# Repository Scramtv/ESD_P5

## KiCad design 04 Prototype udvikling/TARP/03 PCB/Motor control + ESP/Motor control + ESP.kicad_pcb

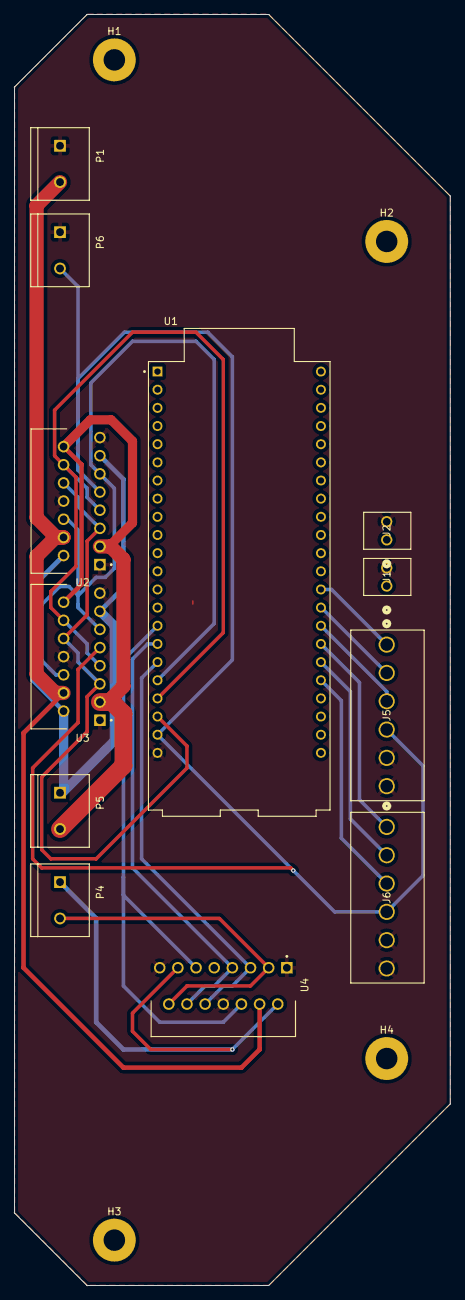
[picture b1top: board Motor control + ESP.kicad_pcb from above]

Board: 2 copper layers, 61.0 x 177.8 mm, 16 parts (0 on the bottom side), 21 nets.

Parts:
H1, H2, H3, H4: MountingHole; MountingHole_3mm_Pad
J1: Button in2; CONN_A-6373-02A_MOL
J2: Button in1; CONN_A-6373-02A_MOL
J5: Encoder1; CONN_SDA-41791_M450_06_MOL
J6: Encoder2; CONN_SDA-41791_M450_06_MOL
P1: Volt supply; TE_282837-2
P4: Motor out2; TE_282837-2
P5: Motor out1; TE_282837-2
P6: Power in; TE_282837-2
U1: ESP32-S3-DEVKITM-1-N8; MODULE_ESP32-S3-DEVKITM-1-N8
U2, U3, U4: L298N; TO127P2020X500X2100-15

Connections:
+5V: J5.4, J6.4, P6.2, U1.J1_21 (5V0), U2.9 (Vss), U3.9 (Vss)
+12V: P1.2, U2.4 (Vs), U3.4 (Vs), U4.4 (Vs)
<NO NET>: J1.2, J2.2, J5.5, J5.6, J6.5, J6.6, P1.1, P6.1, U1.J1_22 (GND_J1_22), U2.1 (SENSE_A), U2.8 (GND), U2.15 (SENSE_B), U3.1 (SENSE_A), U3.8 (GND), U3.15 (SENSE_B), U4.1 (SENSE_A), U4.8 (GND), U4.15 (SENSE_B)
unnamed: U1.J1_15 (GPIO13), U4.6 (EnA), U4.11 (EnB)
unnamed: U1.J1_16 (GPIO14), U4.7 (IN2), U4.12 (IN4)
unnamed: U1.J1_17 (GPIO15), U4.5 (IN1), U4.10 (IN3)
unnamed: U1.J1_18 (GPIO16), U2.6 (EnA), U2.11 (EnB), U3.6 (EnA), U3.11 (EnB)
unnamed: U1.J1_19 (GPIO17), U2.7 (IN2), U2.12 (IN4), U3.7 (IN2), U3.12 (IN4)
unnamed: U1.J1_20 (GPIO18), U2.5 (IN1), U2.10 (IN3), U3.5 (IN1), U3.10 (IN3)
unnamed: J6.3, U1.J3_18 (GPIO21)
unnamed: J6.2, U1.J3_17 (GPIO26)
unnamed: J6.1, U1.J3_16 (GPIO33)
unnamed: J5.3, U1.J3_15 (GPIO34)
unnamed: J5.2, U1.J3_14 (GPIO35)
unnamed: J5.1, U1.J3_13 (GPIO36)
unnamed: J1.1, U1.J3_12 (GPIO37)
unnamed: J2.1, U1.J3_11 (GPIO38)
unnamed: P5.1, U2.2 (OUT1), U2.13 (OUT3), U3.2 (OUT1), U3.13 (OUT3)
unnamed: P5.2, U2.3 (OUT2), U2.14 (OUT4), U3.3 (OUT2), U3.14 (OUT4)
unnamed: P4.1, U4.2 (OUT1), U4.13 (OUT3)
unnamed: P4.2, U4.3 (OUT2), U4.14 (OUT4)

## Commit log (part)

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2025-10-28 Antenna 0 and 1 CST (1 til1)
2025-10-28 Matlab plotter til antenne 0 og 1
2025-10-28 Opdateringf motor parameter test
    Opdatering af matlab fill og slet dublicate script
2025-10-28 Antenne Matlab - plotter og data
2025-10-28 Data til model af tilt motor inkl. behandling
2025-10-29 Parameter kode opdateret til support af "tick" pin
    Udover det er koden også generelt opryddet, så vi kun har de funktioner der er blevet brugt
2025-10-29 Model for både Azi og tilt motor inkl. load
2025-10-30 Gaintest Antenna1
2025-10-30 PNG files of simulated and measured S-11 of Antenna 0 and titlechanges for corresponding matlab script
2025-10-30 TARP Motor code v1.1 - WORKS
    - Added state machine
    - works, but does not constantly keep in check with its position. If it is moved, it does not auto correct
2025-10-30 1x2 fælles kanal m. stub
2025-10-30 Referat fra vejledermøde 30-10-2025
2025-10-30 Forbedret formatering
2025-10-31 1x2Antenne V1
    Både opdateret sim og pcb
2025-11-03 Udregning og sim af P +(lead) controller til TARP
    NB lead er ikke helt færdig, men vi starter med at dokumentere P-controlleren
2025-11-03 Ugentlig opdatering af tidsplan iht. møde.
2025-11-03 Oprydning af filer
    TBH ved ikke helt hvordan denne har fundet vej til git, men den ryger ned nu :)
2025-11-04 Ændring af filstruktur og opdatering af gamle filer
    Jeg har ændret strukturen af antenne mapperne og slettet gamle ubrugte filer, der ikke indholdte relevante ting.
    Derudover har jeg også opdateret gamle CST filer så de er kompatible med voksen CST
2025-11-04 Draw.io fil brugt til RF front end udvikling
2025-11-04 Sletning af fejl program
2025-11-04 Ændring af fejl i interface guide til gnu
2025-11-04 TARP motor code V1.3
    - added 2 micro second delay to help with short circuit of H-bridge
    - Changed SSID from AP to TARP
2025-11-05 Opdatering af gamle antenne simulering med export af data, samt simulering af array
    Jeg har opdateret de resterende antenne simuleringer til at være kompatible med voksen CSV og eksporteret simuleringerne i txt format.
    Har også lavet hvad der burde blive arrayet.
2025-11-05 Flytning af diagrammer for frontend
2025-11-05 Upload af beam forming scripts
2025-11-05 H-bridge short circuit update
    - matlab with plots of the issue
    -- plots with potential fix of 1k
    -- BJT issue
    --- BJT potential fix with pull down resistors
    - clean up of data
2025-11-05 TARP motor code V1.4
    - Error margin set to 0
    - delay set to 3 microseconds
2025-11-05 Azimut Control test 80.35 Gain + plot
    Control test of TARP with Gain of 80.35
2025-11-05 Simulering af antenne 6 og videre arbejde på antenne mount
    Antenne 6 sigter efter at sænke frekvensen af antenne 5 med 10 MHz og udvide bundbredden i my.
    Der er nu en holder til antennen tegnet i SolidWorks, der skal bare laves noget til at klaske den på TARPen, samt et "låg" til holderen.
2025-11-06 Indsættelse af tidsbegrænsning på aflås lokale og fjernelse af "Læs opgaven"
2025-11-07 Stavefejl i bødesystem
2025-11-07 Test af antenne 4,5, 5.10 og 5.11
2025-11-07 Viderudvikling af front end. Undersøg muligheden for at trække data ud af GNU
2025-11-07 Ekstra figure til proposed solution. (Alså en ny figure men i samme dokument)
2025-11-09 Billeder af fysisk setup
2025-11-09 Omnavngivning og rettelse af regnefejl af motor parametre
2025-11-09 Billede af ustabile hastigheder for tiltmoteren
    NB lavet ved konstant spænding
2025-11-09 Opdatering af overføringsfunktioner, så de nu bruger korrekte modelparametre
2025-11-10 Updated git ignore to disregard matlab autosave
2025-11-10 Script to plot OL bode plot and CL step with P-controller
    Both for azi and tilt
2025-11-10 Ændringer til låget til antenne holderen
    Den er blevet gjort tykkere
2025-11-10 Opdatering så step respons er for 180 grader og ikke 1
2025-11-11 Opdatering af tidsplan iht. dagligt møde
2025-11-12 Serial R/W interface to ESP32
2025-11-13 Opdatering af git ignore til at undlade python temp files
2025-11-13 Interface for direct motor control via serialRW.py
    Can control both tilt and azimuth motor, can also return their position
2025-11-13 Udregninger på modtaget effekt og SNR
    Har slettet min temp maplefil og omdøbt SNR&SignalStrenth. Og selvfølgelig udregnet SNR
2025-11-13 ESP code kan nu håndtere begge kerner
    PT er der intet der kører på kernerne @MiniBeier indsætter sin kode heri
2025-11-13 TARP Motor code V2.0
    - tilt code added
    - new files for azimut, tilt and UART
    - change of button names and interrupts setup
2025-11-13 TARP Azimut step response 3.73 gain
2025-11-13 data fra beamsteering test
    - Jeppe
2025-11-13 TARP Motorcode V3.0
    - Integrated 2 cores
    - currently running one core
2025-11-14 Referat fra vejledermøde d. 13-11-2025
2025-11-14 TARP Motorcode V3.1_kommentarer
    Div. kommentarer. @MiniBeier kigger på disse
2025-11-14 Matlab plots til TARP control test
    - Korrekt gain
    - Kode V3.1 (skal opdateres til nyt kode)
2025-11-15 Slet af fejl kode og opdatering af ny kode
    -Jeppe på pi
2025-11-16 TARP Control code V3.2
    -Added sample rate control
    -Code clean up
    -- removal of state machine
    -- merging of velocity function
    --removal of irrelevant variables and functions
2025-11-16 Data til test af hvad der er galt med breamforming og frontend
    - Jeppe fra RPI
2025-11-17 Krav for detection time og precision
    Lavet på baggrund af krav i teams
2025-11-17 Opdatering af controller udregning
    Korrekte P-værdier
    notat om lead-controller
2025-11-17 Settlingtime for CL azi og tilt
2025-11-18 H-bridge diagram current flow
2025-11-18 TARP Control test of code V3.3
    - Matlab plots
    -- Step response tilt + azi
    - Data
    -- step response tilt + azi
    -- tilt slør
2025-11-19 Bruger korrekte tolerancer og nyt script til med større numerisk præcision
2025-11-19 Opdatering så stepresponse er for 90 grader og ikke 180
2025-11-21 Fix af beregninger
    Havde nogle beregninger der ikek var rigtige, nu er de
2025-11-24 Added zoom for open loop bodeplot
    Based on comment from Jesper
2025-11-24 H-bridge plots and diagram
2025-11-24 TARP PCB and Schematic printout
2025-11-24 TARP Code V3.3 - moving code around
2025-11-24 TARP Control physical test data + plots
2025-11-24 Opdatering af navne på diagrammer for bedre klarhed
2025-11-24 Upload af Sigurds SDR Kode
2025-11-25 Dual RX SDR code
2025-11-25 Opdatering af tidsplan iht. møde
2025-11-25 Dual RX
    This should have no "buffer"issue as before, however unknown, as datahandling hasn't been completed. Update and cleanup will follow
2025-11-26 Bodeplot/stepresponse updated to include grid and target
    For controller
2025-11-26 Indsættelse af enheder
    NB. nu er accelerationen allerede i milli, så vær opmærksom på dette hvis du bruger scriptet
2025-11-27 Slet af fejl data fra Gammel GNU radio program og SDR
    Det er data der er er passede forkert så totalt ubrugligt
2025-11-27 Ændring af GNU program og opdatering data fra programmet (test).
2025-11-27 V3 af RX frontend, gnu+python og med beamforming implamenterde
2025-11-27 Front end V4. code og data fra test + matlab program til at plotte data
2025-11-27 Frontend v4. dual channel + data fra test + matlab program der plotter
2025-11-27 Matlab program til at regne RF-frontend krav
2025-11-27 Referat fra vejledermøde i dag
2025-11-28 PCB til antenne5
2025-12-02 H-bridge shortcircuit plots - axis titles fixed
2025-12-02 Tarp V3.4 - code visual clean up
    Making visually more compact
2025-12-02 NewFolder cleanup
2025-12-02 Test results of unstable PSU
2025-12-04 Ændringer af udregninger af krav til frontend. (Jeg have brugt en forkert resecived power bruger nu den Antenne afsnittet kommer frem til)
2025-12-04 Sampled data from different angles
    From antenna to python
2025-12-05 block diagram for project, drawio
2025-12-05 Block diagram front end
2025-12-05 Opdateret CST simuleringer til Antenneafsnittet, samt Test fr APMS og tilhørende Matab script og figurer til dette
    Også den Calculated Antenne, CST, Matlab og figurer
2025-12-08 Test setup diagram til validation test af frontend
2025-12-08 Kode og data fra validation test af Frontend V.5
2025-12-08 MAtlab til at plotte data fra validation test af Frontend V.5
2025-12-09 Drawio figurer til Antenne dimensioner og tilhørende PNG filer til rapport
    Samt Smith Chart for Antenne 0 og 1 fra CST til rapport
2025-12-09 Upload af beamforming tests og sims
2025-12-09 Sletning af data fra frontend test der er udført forkert V.5
2025-12-09 Validation test af frontend V.5 data hvor testen er udført rigtigt
2025-12-09 Frontend Calibration of gain on channel 2 - data og settings
2025-12-09 Matlab til at plotte data fra calibration of gain on gain 2 og data
2025-12-09 Validation test frontend V5. gain adjusted and lower sample rate
2025-12-09 Plot FFT for not gain adjusted frontend
2025-12-09 Grov databehandling af DAS BF algo phase delay test
2025-12-10 Klargøring af script til indsættelse i LaTeX
    I.e. oprydning og fjernelse af ligegyldige statements
2025-12-10 CST Smith chart simulering for antenne 0 og 1
    Og indsætning af figurer til rapport
2025-12-10 Diagram of setup for bf phase delay test
2025-12-10 Opdateret databehandling af phase delay test BF
    Python brugt til at finde gennemsnit + varians, dette er indsat i maple dokumentet
2025-12-11 Implementation code V1
    Implements all different submodules in there current state. Tested and works -ish. Still issue with BF, but that is explained in the report
2025-12-11 pic of gain test setup and updated drawio gain test setup
2025-12-12 Implementation script V1.1
    Updated values from BF section
2025-12-14 Upload af testkode og data til beamformer
2025-12-15 Fikset akse titler og værdier på figure i forhold til validation test af RF front end
2025-12-15 Figure til test af front end. Dette indholder matlab script til gain calibering og til efter gain calibaring
2025-12-15 Ændring af figure til control af snit. indholder både matlab og sleve figuren. Ændring er at vi har sat flere grafer på samme figure så det er nemt at se indvirkningen
2025-12-15 Flere beamforming testresultater og kodeændringer
2025-12-16 Note ift. raspberry der slukkede
    TBH, lidt ligegyldig nu hvor vi ender med at smide en buck på. Men tænker stadigvæk at beholde dataen i tilfælde af at det skulle blive relevant 👍
2025-12-16 Referat fra dagens vejledermøde
2025-12-17 BF mappe omstruktur upload af testkode
2025-12-18 Upload af testkode filer
2025-12-18 Flytning af figuren
2025-12-18 Ændringer af figure til rf front figuren
2025-12-18 Beamforming kode småtterier
2025-12-18 Use case diagrams
    - update text
    - diagram explanations
2025-12-18 TARP control code - visual clean up
2025-12-18 Control plots and matlab script update
2025-12-18 Noter til antenne teori
2025-12-18 Beamforming test data timing på RPI
    -Jeppe
2025-12-18 Test data fra 0.5 lambda i antenne afstand
    Find ud af hvorfor vinkel er fucked i BF
2025-12-18 ny testkode og data
2025-12-19 PLotter og Figure til BF dump
2025-12-19 SNRplots til BF
2026-01-14 Fix af unresolved edges
2026-01-14 Antenne mount V3
    Nu med 0.5 lambda imellem.
    NB bruger det originale mount til TARP for minimering af ny print -> kræver derfor mindre retrofit i virkeligheden
2026-01-15 Figure til flowchart af løsnig
2026-01-15 Mathlab der regner hvor lang rækkevide vi har
2026-01-15 Opdatering af top support
    Sikre at vi nu har en "ramme" rundt om antennen
2026-01-15 test til BF
    Jeppe skulle teste noget for Noah
2026-01-15 Opdatering af processanalyse pga. af møde
    Møde afhold d. 15-01-2026
2026-01-15 Optimering af ESPkode
    Udkommentering af Wifi
2026-01-15 Main kode V2
    Dette virker nu
    Div useful funcs har fået nogle flere plot funktioner, fft, normalising, offsets
    SDR control er sat til et gain på 20 dB på begge
    Main virker nu, og har fået indsat nogle buffer flushes. Samples også sat ned så vi ikke Overflower
2026-01-19 Fixed beamforming summing instead of taking mean of power
